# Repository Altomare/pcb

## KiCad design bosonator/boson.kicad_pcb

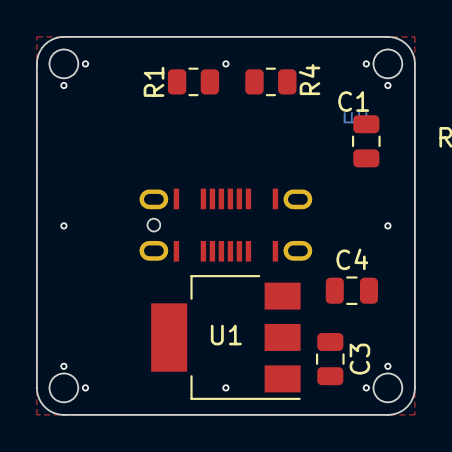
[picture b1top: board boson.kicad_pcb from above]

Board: 2 copper layers, 21.0 x 21.0 mm, 8 parts (1 on the bottom side), 7 nets.

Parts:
C1, C3, C4: 10µ; C_0805_2012Metric
P1: DF40HC(4.0)-80DS-0.4V(51); HRS_DF40HC(4.0)-80DS-0.4V(51)
P2: USB_C_Plug_USB2.0; USB4145-03-0230-C
R1, R4: 5.1k; R_0805_2012Metric
U1: AMS1117-3.3; SOT-223-3_TabPin2

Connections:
+3.3V: C1.1, C3.1, P1.2, P1.4, P1.6, P1.8, P1.15, U1.2 (VO)
/USB_D_N: P1.11, P2.A7 (D-), P2.B7 (D-)
/USB_D_P: P1.9, P2.A6 (D+), P2.B6 (D+)
GND: C1.2, C3.2, C4.2, P1.1, P1.3, P1.5, P1.7, P1.10, P1.13, P1.19, P1.20, P1.29, P1.30, P1.39, P1.40, P1.49, P1.50, P1.59, P1.60, P1.69, P1.70, P2.A1 (GND), P2.A12 (GND), P2.B1 (GND), P2.B12 (GND), R1.2, R4.2, U1.1 (GND)
unnamed: P2.A5 (CC1), R1.1
unnamed: P2.B5 (CC2), R4.1
unnamed: C4.1, P2.A4 (VBUS), P2.A9 (VBUS), P2.B4 (VBUS), P2.B9 (VBUS), U1.3 (VI)

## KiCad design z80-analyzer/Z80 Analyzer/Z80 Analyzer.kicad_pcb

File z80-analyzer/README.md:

# Pin assignment

| Hantek | pin | Z80   |
| ------ | --- | ----- |
| GND    | 1   | GND   |
| GND    | 2   | GND   |
| ACLK   | 3   | CLK   |
| BCLK   | 4   | CLK   |
| GND    | 5   | GND   |
| GND    | 6   | GND   |
| A0     | 7   | NMI   |
| B0     | 8   | IORQ  |
| A1     | 9   | INT   |
| B1     | 10  | RD    |
| A2     | 11  | RESET |
| B2     | 12  | MREQ  |
| A3     | 13  | D1    |
| B3     | 14  | WR    |
| A4     | 15  | A0    |
| B4     | 16  | D0    |
| A5     | 17  | A1    |
| B5     | 18  | M1    |
| A6     | 19  | D6    |
| B6     | 20  | D7    |
| A7     | 21  | A2    |
| B7     | 22  | D2    |
| A8     | 23  | D4    |
| B8     | 24  | D5    |
| A9     | 25  | A5    |
| B9     | 26  | D3    |
| A10    | 27  | A6    |
| B10    | 28  | A3    |
| A11    | 29  | A15   |
| B11    | 30  | A4    |
| A12    | 31  | A12   |
| B12    | 32  | A14   |
| A13    | 33  | A9    |
| B13    | 34  | A7    |
| A14    | 35  | A10   |
| B14    | 36  | A8    |
| A15    | 37  | A11   |
| B15    | 38  | A13   |
| AST0   | 39  |       |
| AST1   | 40  |       |

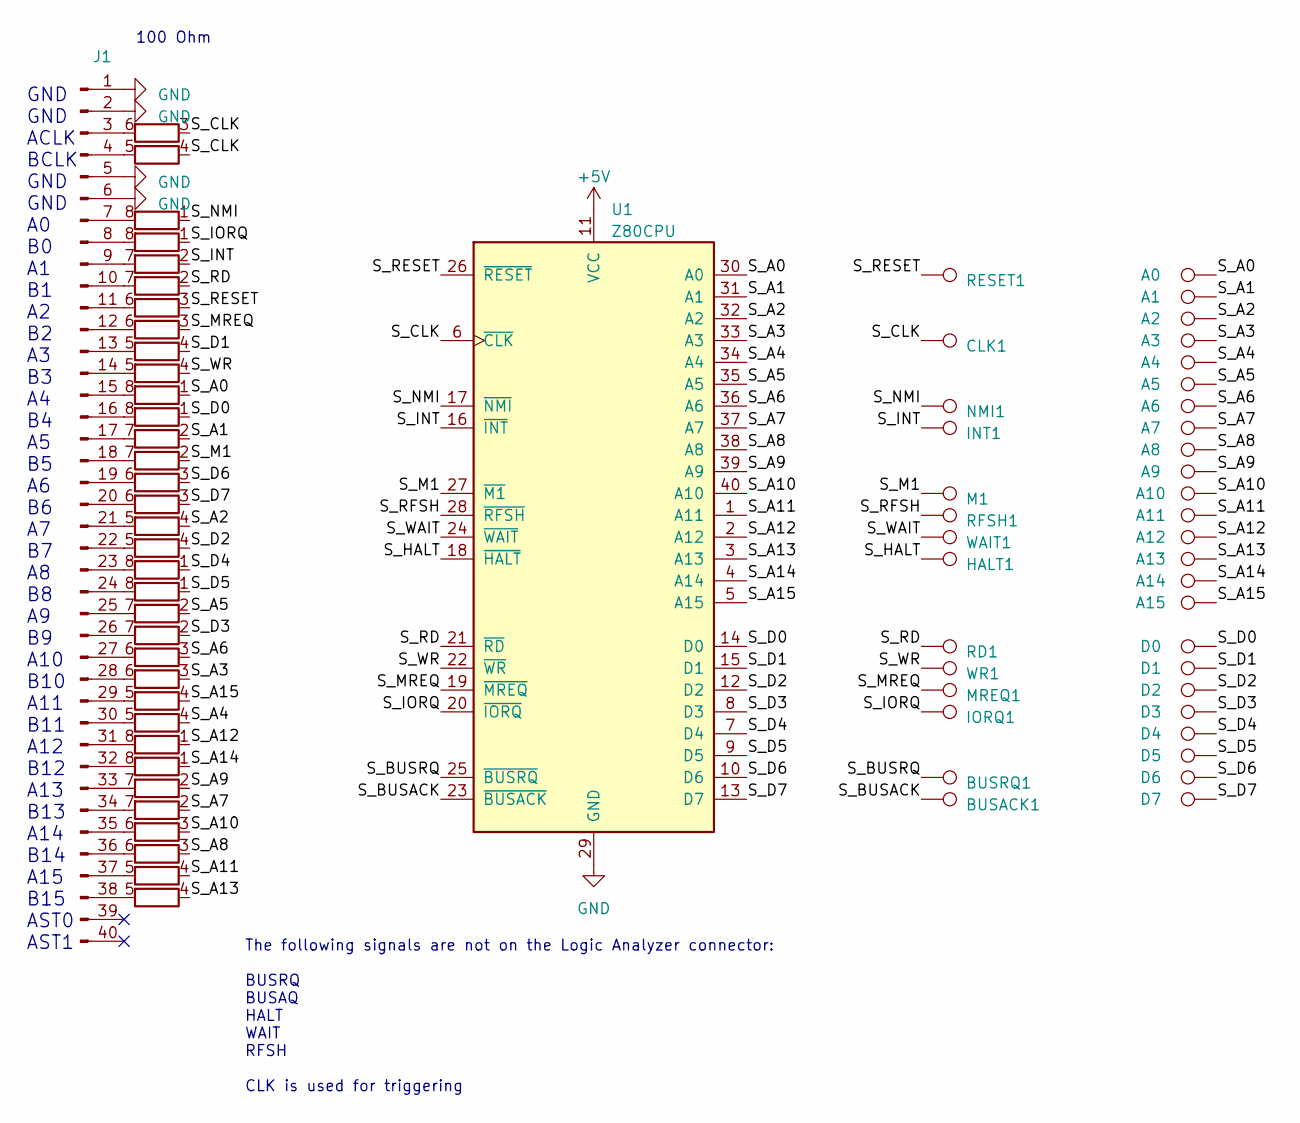
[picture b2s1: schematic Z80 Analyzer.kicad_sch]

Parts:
A0, A1, A2, A3, A4, A5, A6, A7, A8, A9, A10, A11, A12, A13, A14, A15: TestPoint; TestPoint_Keystone_5021
BUSACK1: TestPoint; TestPoint_Keystone_5021
BUSRQ1: TestPoint; TestPoint_Keystone_5021
CLK1: TestPoint; TestPoint_Keystone_5021
D0, D1, D2, D3, D4, D5, D6, D7: TestPoint; TestPoint_Keystone_5021
HALT1: TestPoint; TestPoint_Keystone_5021
INT1: TestPoint; TestPoint_Keystone_5021
IORQ1: TestPoint; TestPoint_Keystone_5021
J1: Conn_01x40_Pin; IDC-Header_2x20_P2.54mm_Vertical
M1: TestPoint; TestPoint_Keystone_5021
MREQ1: TestPoint; TestPoint_Keystone_5021
NMI1: TestPoint; TestPoint_Keystone_5021
RD1: TestPoint; TestPoint_Keystone_5021
RESET1: TestPoint; TestPoint_Keystone_5021
RFSH1: TestPoint; TestPoint_Keystone_5021
RN1, RN3, RN4, RN5, RN7, RN8, RN9: R_Pack04_SIP_Split; R_Array_Convex_4x0603
RN2, RN6: R_Pack04_Split; R_Array_Convex_4x0603
U1: Z80CPU; DIP-40_W15.24mm_Socket
WAIT1: TestPoint; TestPoint_Keystone_5021
WR1: TestPoint; TestPoint_Keystone_5021

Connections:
+5V: U1.11 (VCC)
/S_A0: A0.1, RN1.1 (R1.1), U1.30 (A0)
/S_A1: A1.1, RN1.2 (R2.1), U1.31 (A1)
/S_A2: A2.1, RN1.4 (R4.1), U1.32 (A2)
/S_A3: A3.1, RN7.3 (R3.1), U1.33 (A3)
/S_A4: A4.1, RN7.4 (R4.1), U1.34 (A4)
/S_A5: A5.1, RN3.2 (R2.1), U1.35 (A5)
/S_A6: A6.1, RN3.3 (R3.1), U1.36 (A6)
/S_A7: A7.1, RN8.2 (R2.1), U1.37 (A7)
/S_A8: A8.1, RN8.3 (R3.1), U1.38 (A8)
/S_A9: A9.1, RN4.2 (R2.1), U1.39 (A9)
/S_A10: A10.1, RN4.3 (R3.1), U1.40 (A10)
/S_A11: A11.1, RN4.4 (R4.1), U1.1 (A11)
/S_A12: A12.1, RN4.1 (R1.1), U1.2 (A12)
/S_A13: A13.1, RN8.4 (R4.1), U1.3 (A13)
/S_A14: A14.1, RN8.1 (R1.1), U1.4 (A14)
/S_A15: A15.1, RN3.4 (R4.1), U1.5 (A15)
/S_BUSACK: BUSACK1.1, U1.23 (~BUSACK)
/S_BUSRQ: BUSRQ1.1, U1.25 (~BUSRQ)
/S_CLK: CLK1.1, RN9.3 (R3.1), RN9.4 (R4.1), U1.6 (~CLK)
/S_D0: D0.1, RN6.1 (R1.1), U1.14 (D0)
/S_D1: D1.1, RN2.4 (R4.1), U1.15 (D1)
/S_D2: D2.1, RN6.4 (R4.1), U1.12 (D2)
/S_D3: D3.1, RN7.2 (R2.1), U1.8 (D3)
/S_D4: D4.1, RN3.1 (R1.1), U1.7 (D4)
/S_D5: D5.1, RN7.1 (R1.1), U1.9 (D5)
/S_D6: D6.1, RN1.3 (R3.1), U1.10 (D6)
/S_D7: D7.1, RN6.3 (R3.1), U1.13 (D7)
/S_HALT: HALT1.1, U1.18 (~HALT)
/S_INT: INT1.1, RN2.2 (R2.1), U1.16 (~INT)
/S_IORQ: IORQ1.1, RN5.1 (R1.1), U1.20 (~IORQ)
/S_M1: M1.1, RN6.2 (R2.1), U1.27 (~M1)
/S_MREQ: MREQ1.1, RN5.3 (R3.1), U1.19 (~MREQ)
/S_NMI: NMI1.1, RN2.1 (R1.1), U1.17 (~NMI)
/S_RD: RD1.1, RN5.2 (R2.1), U1.21 (~RD)
/S_RESET: RESET1.1, RN2.3 (R3.1), U1.26 (~RESET)
/S_RFSH: RFSH1.1, U1.28 (~RFSH)
/S_WAIT: U1.24 (~WAIT), WAIT1.1
/S_WR: RN5.4 (R4.1), U1.22 (~WR), WR1.1
GND: J1.1, J1.2, J1.5, J1.6, U1.29 (GND)
unnamed: J1.3, RN9.6 (R3.2)
unnamed: J1.4, RN9.5 (R4.2)
unnamed: J1.7, RN2.8 (R1.2)
unnamed: J1.8, RN5.8 (R1.2)
unnamed: J1.9, RN2.7 (R2.2)
unnamed: J1.10, RN5.7 (R2.2)
unnamed: J1.11, RN2.6 (R3.2)
unnamed: J1.12, RN5.6 (R3.2)
unnamed: J1.13, RN2.5 (R4.2)
unnamed: J1.14, RN5.5 (R4.2)
unnamed: J1.15, RN1.8 (R1.2)
unnamed: J1.16, RN6.8 (R1.2)
unnamed: J1.17, RN1.7 (R2.2)
unnamed: J1.18, RN6.7 (R2.2)
unnamed: J1.19, RN1.6 (R3.2)
unnamed: J1.20, RN6.6 (R3.2)
unnamed: J1.21, RN1.5 (R4.2)
unnamed: J1.22, RN6.5 (R4.2)
unnamed: J1.23, RN3.8 (R1.2)
unnamed: J1.24, RN7.8 (R1.2)
unnamed: J1.25, RN3.7 (R2.2)
unnamed: J1.26, RN7.7 (R2.2)
unnamed: J1.27, RN3.6 (R3.2)
unnamed: J1.28, RN7.6 (R3.2)
unnamed: J1.29, RN3.5 (R4.2)
unnamed: J1.30, RN7.5 (R4.2)
unnamed: J1.31, RN4.8 (R1.2)
unnamed: J1.32, RN8.8 (R1.2)
unnamed: J1.33, RN4.7 (R2.2)
unnamed: J1.34, RN8.7 (R2.2)
unnamed: J1.35, RN4.6 (R3.2)
unnamed: J1.36, RN8.6 (R3.2)
unnamed: J1.37, RN4.5 (R4.2)
unnamed: J1.38, RN8.5 (R4.2)

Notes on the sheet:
100 Ohm
The following signals are not on the Logic Analyzer connector: BUSRQ BUSAQ HALT WAIT RFSH CLK is used for triggering
GND GND ACLK BCLK GND GND A0 B0 A1 B1 A2 B2 A3 B3 A4 B4 A5 B5 A6 B6 A7 B7 A8 B8 A9 B9 A10 B10 A11 B11 A12 B12 A13 B13 A14 B14 A15 B15 AST0 AST1

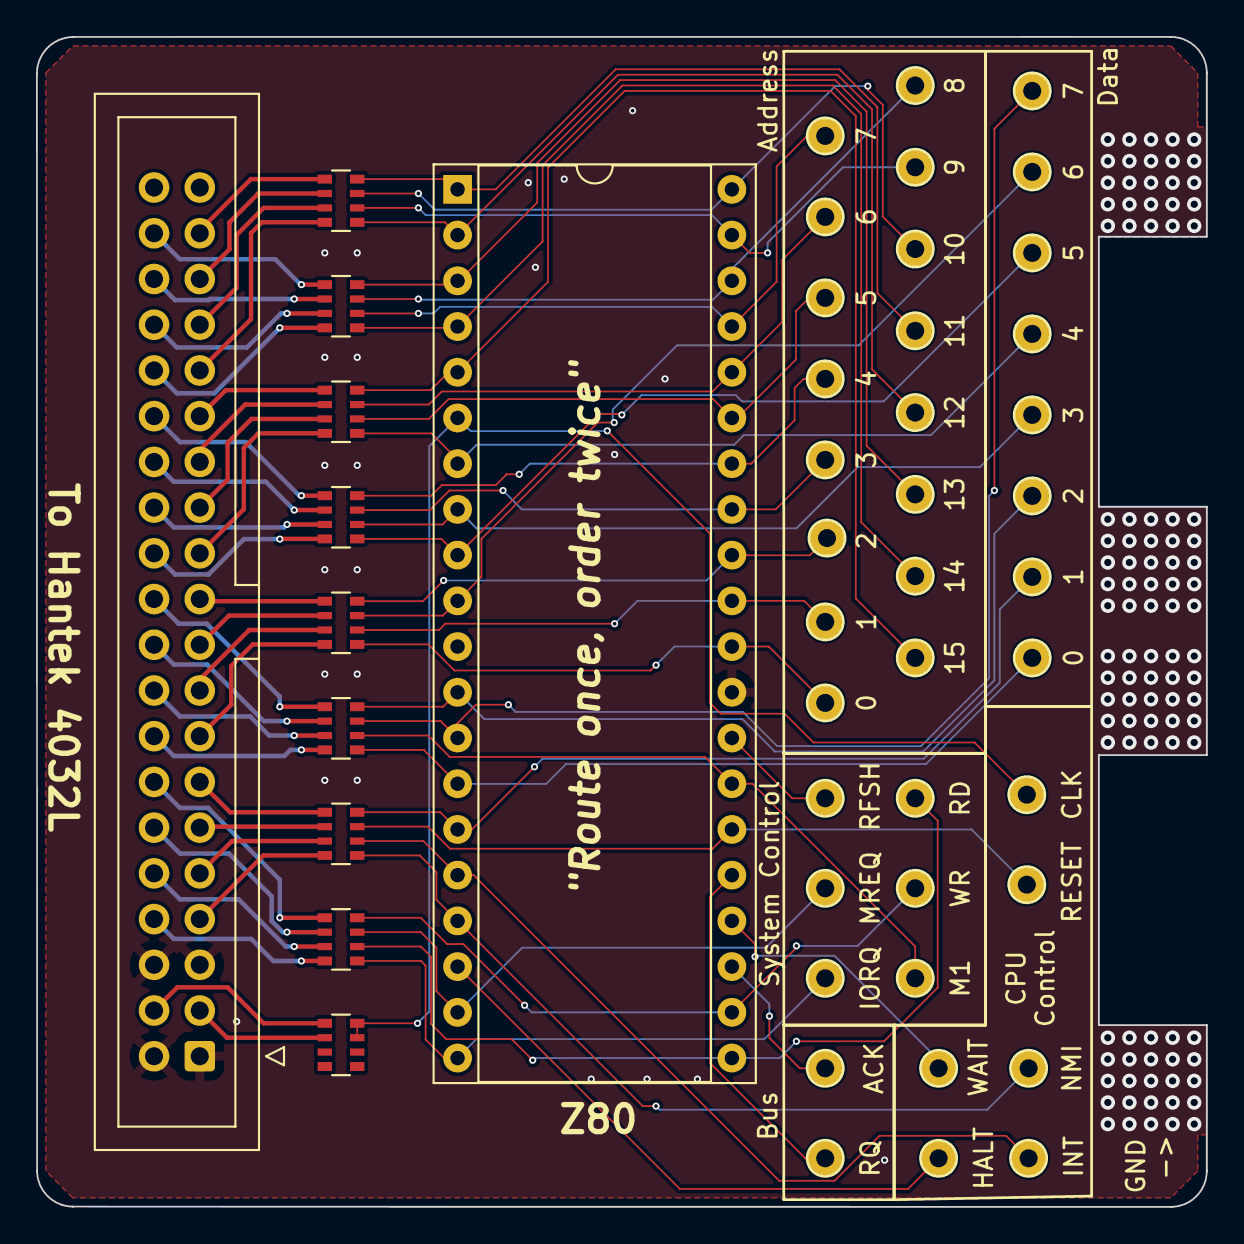
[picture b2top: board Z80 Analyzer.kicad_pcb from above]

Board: 2 copper layers, 65.0 x 65.0 mm, 49 parts (0 on the bottom side), 73 nets.

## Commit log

2023-04-16 Rudimentary .gitignore
2023-04-16 [Boson] First import
2023-04-16 [Z80] First import
2023-04-17 [Z80] Layout update
    Mostly done, missing:
    * Size
    * Aligned slots for socket stack securing
    * Grounding lead pads
2023-04-17 [Z80] Layout done
    Needs ground vias, routing and some easter eggs
2023-05-01 [Z80] New routing, just needs rechecking now
2023-05-01 Add gerber output to gitignore
2023-05-01 [Boson] Quick & dirty routing
2023-05-02 Remove nested directories
2023-08-27 [Z80] Add pin assignment table
2023-11-10 [Boson] Misc. WIP bad.
